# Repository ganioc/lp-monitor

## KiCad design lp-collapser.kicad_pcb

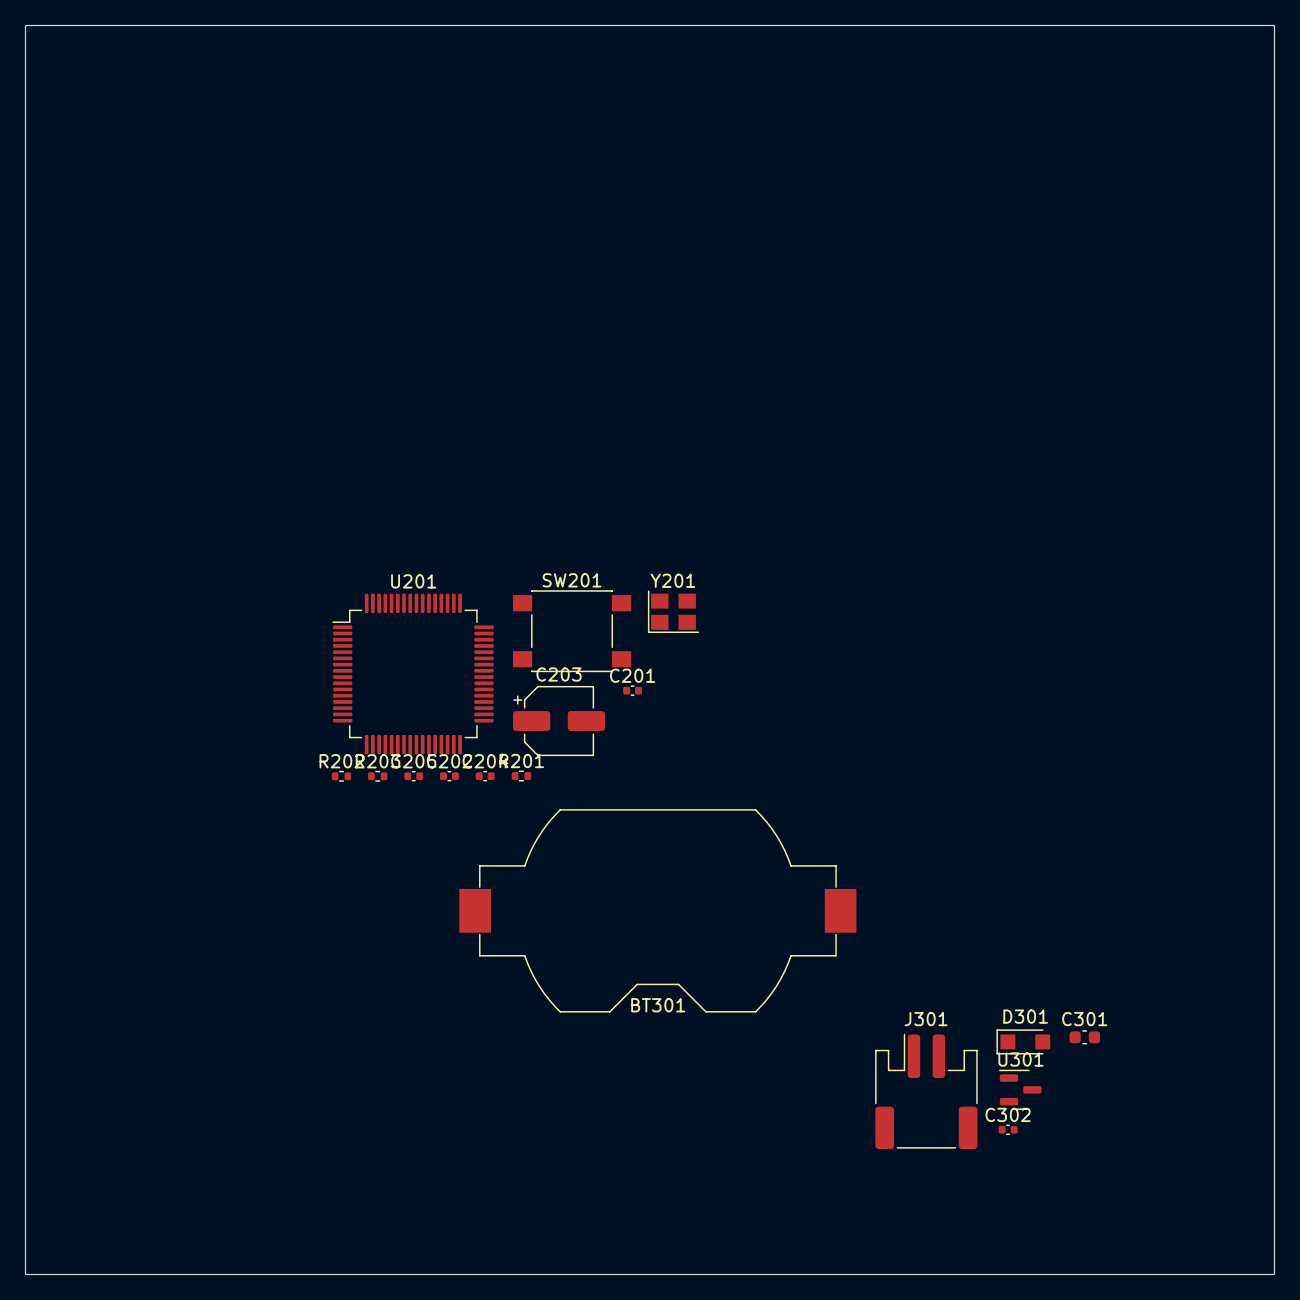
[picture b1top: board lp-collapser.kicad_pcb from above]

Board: 2 copper layers, 100.3 x 100.3 mm, 17 parts (0 on the bottom side), 11 nets, no tracks yet.

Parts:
BT301: Battery_Cell; BatteryHolder_Keystone_1058_1x2032
C201, C202: 6p8; C_0402_1005Metric
C203: 220uF; CP_Elec_5x3
C204: 10pF; C_0402_1005Metric
C205: 22nF; C_0402_1005Metric
C301: 1uF; C_0603_1608Metric
C302: 1uF; C_0402_1005Metric
D301: PMEG6020AELR; Nexperia_CFP3_SOD-123W
J301: Conn_01x02; JST_PH_S2B-PH-SM4-TB_1x02-1MP_P2.00mm_Horizontal
R201, R202: 0Ohm; R_0402_1005Metric
R203: 1KOhm; R_0402_1005Metric
SW201: SW_Push; SW_Push_1P1T_NO_6x6mm_H9.5mm
U201: STM32L431RCTx; LQFP-64_10x10mm_P0.5mm
U301: MCP1700-1202E_SOT23; SOT-23
Y201: 32.768K; Crystal_SMD_3225-4Pin_3.2x2.5mm

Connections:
/mcu/BATT_Backup: BT301.1 (+), U201.1 (VBAT)
/mcu/VCC_2V8: U201.13 (VDDA), U201.19 (VDD), U201.32 (VDD), U201.48 (VDD), U201.64 (VDD)
/power/+VBATT: C301.1, D301.1 (K), J301.1, U301.3 (VI)
/power/VCC_3V: C302.1, U301.2 (VO)
GND: BT301.2 (-), C201.2, C202.2, C203.2, C204.2, C205.2, C301.2, C302.2, D301.2 (A), J301.2, SW201.1, U201.12 (VSSA), U201.18 (VSS), U201.31 (VSS), U201.47 (VSS), U201.63 (VSS), U301.1 (GND)
unnamed: C201.1, R201.2, Y201.1
unnamed: C202.1, R202.2, Y201.2
unnamed: C204.1, R203.2, SW201.2
unnamed: C205.1, R203.1, U201.7 (NRST)
unnamed: R201.1, U201.3 (PC14)
unnamed: R202.1, U201.4 (PC15)

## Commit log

2022-05-26 1st commit
2022-05-26 Add README.md
